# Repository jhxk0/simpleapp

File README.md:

# Drone stack: F405 flight controller + 4-in-1 AM32 ESC

Two KiCad 9 boards for a 5" quad, 30.5 x 30.5 mm M3 mounting.

| Board | Size | Layers | Key parts |
|---|---|---|---|
| `fc/`  flight controller | 36 x 36 mm | 4 (1 oz) | STM32F405RGT6, ICM-42688-P, BMP280, W25Q128 16 MB, LMR33630 5 V/3 A buck, USB-C |
| `esc/` 4-in-1 ESC (rev C) | 46 x 46 mm | 6 (2 oz outer, >=1 oz inner) | 4x STM32G071K8U6N (AM32), 12x LM2105, 24x CSD18543Q3A 60 V |

**Status:** the FC is complete: ERC clean, DRC clean with schematic parity, and fab files generated.
The ESC **schematic** is complete and ERC clean. Its **layout is about 95 % routed and DRC-clean apart from
29 open signal connections**, so it **must not be ordered yet**. See "ESC layout status" below.

Input: 3-6S LiPo. Both boards are generated from Python sources in `tools/`. Edit `tools/*_design.py`
(circuit) or `tools/*_layout.py` (placement), then rebuild; don't hand-edit the generated files unless
you're taking over in the KiCad GUI from here (which is fine — they are normal KiCad 9 projects).

## Files

```
fc/fc.kicad_pro, .kicad_sch, .kicad_pcb     KiCad 9 project (open in KiCad 9+)
fc/fc-schematic.pdf                         schematic
fc/fab/fc-gerbers.zip                       Gerbers + drill -> upload to the PCB fab
fc/fab/fc-BOM-jlcpcb.csv, fc-CPL-jlcpcb.csv JLCPCB assembly files
fc/fab/fc-BOM-full.csv                      BOM with MPNs and sourcing status
fc/drc.json, fc/erc.json                    last DRC / ERC reports
esc/esc.kicad_sch, esc-schematic.pdf        ESC schematic (complete)
esc/esc.kicad_pcb                           ESC layout, WIP: fully placed, power + gate drive done, 29 signal links open
tools/                                      generators (see "Rebuilding")
```

## FC <-> ESC link (8-pin JST-SH 1.0 mm, same pinout on both boards)

| Pin | 1 | 2 | 3 | 4 | 5 | 6 | 7 | 8 |
|---|---|---|---|---|---|---|---|---|
| Signal | VBAT | GND | CURR | TLM | M1 | M2 | M3 | M4 |

Use a straight-through cable (pin 1 to pin 1). This is *not* guaranteed to match third-party ESCs —
check before plugging the FC into anything else. This ESC has no current sensor: CURR (pin 3) is not
connected, so disable the current meter in firmware (or use a third-party ESC that provides it).
TLM is not driven either; use bidirectional DShot for RPM telemetry.
The SH contacts are rated ~1 A: power a high-draw VTX from the battery pads, not through the FC.

## Flight controller pinout (STM32F405RGT6) — for your firmware

| Function | Pins | Peripheral |
|---|---|---|
| IMU ICM-42688-P | PA5 SCK, PA6 MISO, PA7 MOSI, PA4 CS, PC4 INT1 | SPI1 |
| Flash W25Q128 (blackbox) | PC10 SCK, PC11 MISO, PC12 MOSI, PA15 CS | SPI3 |
| Baro BMP280 (addr 0x76) + GPS compass | PB8 SCL, PB9 SDA (2.2k pull-ups) | I2C1 |
| Motors M1-M4 (DShot) | PB0, PB1, PC8, PC9 | TIM3 CH3/CH4, TIM8 CH3/CH4 |
| Receiver (JST "RX") | PA9 TX, PA10 RX | USART1 |
| GPS (JST "GPS") | PA2 TX, PA3 RX | USART2 |
| VTX / MSP (JST "VTX") | PB10 TX, PB11 RX; PC7 = SBUS-in pin 6 | USART3, USART6 RX |
| Spare pads TX4/RX4, TX6 | PA0, PA1, PC6 | UART4, USART6 TX |
| ESC telemetry | PD2 | UART5 RX (RX only — PC12 is used by SPI3) |
| LED strip | PA8 (33 R series) | TIM1 CH1 |
| Buzzer (low-side FET, BZ+ = 5 V) | PB6 | TIM4 CH1 |
| Status LEDs (active high) | PB4 blue, PB5 green | |
| VBAT sense | PC2, divider 10k/1k (x11) | ADC |
| Current sense from ESC | PC1 (1k + 100 nF) | ADC |
| USB detect | PC5, divider 10k/20k from VBUS | |
| USB FS | PA11 D-, PA12 D+ | OTG_FS (no VBUS sensing on PA9) |
| HSE | 8 MHz crystal | |
| Boot | BOOT button -> BOOT0 (DFU over USB) ; SWD pads DIO/CLK/RST/3V3/GND on the bottom | |

Power: VBAT -> LMR33630 buck -> +5 V (also fed from USB through a Schottky) -> two AP2112K-3.3
LDOs (one for MCU/peripherals, one dedicated to the IMU).

## ESC firmware

Each channel is pin-for-pin compatible with AM32 target **JUPITER_80_G071**
(`HARDWARE_GROUP_G0_L`, current ADC PA4, voltage ADC PA5, `TARGET_VOLTAGE_DIVIDER 285`), checked
against `Inc/targets.h` and `Mcu/g071/Src/comparator.c` in the AM32 repository:

| Function | G071 pin |
|---|---|
| Phase A/B/C high | PA10 / PA9 / PA8 (TIM1 CH3/CH2/CH1) |
| Phase A/B/C low | PB15 / PB0 / PA7 (TIM1 CH3N/CH2N/CH1N) |
| Signal in (DShot) | PC6 (TIM3 CH1) |
| BEMF A / B / C | PA0 (COMP1 INM) / PA2 (COMP2 INM) / PB7 (COMP2 INM) |
| Virtual neutral | PA1 (COMP1 INP) and PA3 (COMP2 INP), formed from the three divided BEMF signals (3 x 10k) |
| Voltage sense | PA5, 27.4k/1k (x28.4) |

The driver (LM2105) has non-inverting high and low inputs, matching AM32's default (no `USE_INVERTED_LOW`).
Flash the AM32 bootloader to each MCU once through its SWD pads (DIO*n*, CLK*n*, 3V3_*n*, GND on the
bottom), then use the normal AM32 configurator through the FC passthrough. Set dead time and motor
parameters in the configurator; the target's `MILLIVOLT_PER_AMP` is irrelevant because per-ESC current
is not sensed (PA4 is tied low).

Gates are driven directly by the LM2105 (no gate resistors); NRST is left to the internal reset circuit.

Rating: CSD18543Q3A is 60 V / 8.1 mOhm. Treat the board as **~30 A burst / ~20 A continuous per motor
with airflow**. Fine for typical 5" builds; not for high-kV 6S racing setups.

## ESC layout status (rev C, routing unfinished)

Rev C reworks the layout so the power stage routes deterministically:

- 46 x 46 mm (was 44), same 30.5 mm M3 holes: the extra millimetre per side gives the corners, where two
  ESCs' drivers meet, room for their bypass caps and input escapes.
- 6-layer stack-up: F power stage | In1 GND plane | In2, In3 signals | In4 VBAT plane | B control.
- Battery pads in the centre feed the GND/VBAT planes through 35 vias each.
- **Every half-bridge uses one fixed, hand-designed copper pattern**, rotated to all 12 positions:
  low-side gate straight down the F channel between the VBAT/GND feed strips; high-side gate and the
  switch node through that channel's gap on In2/In3 to vias beside the driver; boot cap, VDD bypass,
  driver ground and the HI/LI input escapes all fixed. These 48 driver-to-FET links were what stalled
  rev B; they are now complete and DRC-clean.
- Back-EMF dividers sit on the bottom under the FETs and leave through the bottom channel; the virtual
  neutral is formed at each MCU from the divided signals (3 x 10k), so no neutral wiring runs along the edges.
- "No tracks" rule areas keep routing out of the phase pours and feed strips.

Not done: **29 open connections on the MCU side** (neutral, PWM, SIG, voltage sense, 3.3 V, a few supplies),
mostly around the four MCUs on the bottom. Freerouting gets to ~29 after the MCU support parts were anchored to their pins; the extra grid router
(`tools/finish_route.py`) pre-routes the long PWM/BEMF lines but does not close the rest. The inner
layers still have plenty of free space, so these are ordinary short links. Two ways to finish:

1. In KiCad: open `esc/esc.kicad_pcb`, press `B` to refill zones, run DRC and route the listed
   unconnected items by hand. In2/In3 are mostly empty.
2. Improve the automation (a negotiated-congestion router, or moving the MCUs off the battery pads'
   footprint so their pins can drop vias directly), then `python3 tools/pipeline.py esc route`.

The FC also works with any off-the-shelf 30.5 mm 4-in-1 ESC (check its 8-pin pinout against the table above).

## Before you order — verification checklist

These could not be checked from inside the design environment (no access to datasheet sites or the
JLCPCB/LCSC catalogue). Each is a short check:

1. **ICM-42688-P footprint and reserved pins.** The design uses KiCad's generic
   `LGA-14_3x2.5mm_P0.5mm` footprint and leaves RESV pins 2, 3, 7, 10, 11 unconnected. Compare pin 1
   location, pad sizes and the RESV recommendations against the TDK datasheet.
2. **LCSC part numbers.** `*-BOM-full.csv` marks every line as *recalled* (from memory, likely right),
   *unverified* or *MISSING*. JLCPCB's BOM upload shows the actual match; pick equivalents for the
   missing lines (mostly 50 V caps and ESC silicon).
3. **Assembly rotations.** JLCPCB's parts library sometimes uses a different zero-rotation than KiCad
   (QFN, SOT-23, connectors). Check the placement preview at order time and rotate as needed.
4. **(ESC) Gate-drive LDO margin.** L78L10 is rated 30 V input; 6S is 25.2 V. The 22 R + 1 uF filter helps,
   but a **low-ESR electrolytic (35 V, 470–1000 uF) across the battery pads is mandatory**.
5. **First power-up.** Use a current-limited supply (or smoke stopper), no props, one board at a time.

## Ordering (JLCPCB)

- FC: 4 layers, 1.6 mm, 1 oz, upload `fc/fab/fc-gerbers.zip`; assembly on **both sides** with the BOM and CPL.
- Minimums used: 0.1 mm track, 0.127 mm space, 0.3/0.5 mm vias — within JLCPCB's standard 4-layer capability.
- Stack-up: In1 = solid GND reference plane; In2 = signals + GND fill. Pick JLC's standard 4-layer stack-up.

## Rebuilding

Requires KiCad 9 (`kicad-cli` and the `pcbnew` Python module), Java 25 and Freerouting 2.4.1. The tools
find them automatically on Linux, macOS and Windows; otherwise set `KICAD_CLI`, `KICAD_PYTHON`,
`FREEROUTING_JAR` and `JAVA` (see `tools/kienv.py`).

```
python3 tools/pipeline.py fc sch          # schematic + ERC + netlist cross-check
python3 tools/pipeline.py fc route 80 3   # place, fanout, Freerouting, pours, DRC (retries until clean)
python3 tools/pipeline.py fc fab          # Gerbers, drill, BOM, CPL, renders
```

`pipeline.py esc ...` runs the same steps for the ESC (it also pre-routes the PWM/BEMF lines and runs
the finishing router).

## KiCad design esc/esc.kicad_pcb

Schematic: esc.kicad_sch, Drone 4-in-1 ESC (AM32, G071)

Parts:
C1, C2, C3, C4, C18, C29, C40, C51: 10uF 50V; C_1206_3216Metric; MPN 1206 10uF 50V X5R/X7R
C5, C7: 1uF 50V; C_0805_2012Metric; MPN 0805 1uF 50V X5R/X7R
C6, C8, C9, C12, C14, C16, C20, C23, C25, C27, C31, C34, C36, C38, C42, C45, C47, C49: 1uF 25V; C_0603_1608Metric; MPN 0603 1uF 25V X5R/X7R
C10, C21, C32, C43: 1uF; C_0402_1005Metric; MPN 0402 1uF X5R/X7R; LCSC C52923
C11, C22, C33, C44: 100nF; C_0402_1005Metric; MPN 0402 100nF X5R/X7R; LCSC C1525
C13, C15, C17, C24, C26, C28, C35, C37, C39, C46, C48, C50: 220nF; C_0402_1005Metric; MPN 0402 220nF X5R/X7R
C19, C30, C41, C52: 100nF 50V; C_0603_1608Metric; MPN 0603 100nF 50V X5R/X7R
H1, H2, H3, H4: M3; MountingHole_3.2mm_M3
J1: FC; JST_SH_SM08B-SRSS-TB_1x08-1MP_P1.00mm_Horizontal; MPN SM08B-SRSS-TB
Q1, Q2, Q3, Q4, Q5, Q6, Q7, Q8, Q9, Q10, Q11, Q12, Q13, Q14, Q15, Q16, Q17, Q18, Q19, Q20, Q21, Q22, Q23, Q24: CSD18543Q3A; VSON-8_3.3x3.3mm_P0.65mm_NexFET; MPN CSD18543Q3A
R1, R2: 22; R_0603_1608Metric; MPN 0603 22 1%; LCSC C25092
R3, R15, R27, R39: 100; R_0402_1005Metric; MPN 0402 100 1%; LCSC C25076
R4, R16, R28, R40: 27.4k; R_0402_1005Metric; MPN 0402 27.4k 1%
R5, R17, R29, R41: 1k; R_0402_1005Metric; MPN 0402 1k 1%; LCSC C11702
R6, R9, R12, R18, R21, R24, R30, R33, R36, R42, R45, R48: 18k; R_0402_1005Metric; MPN 0402 18k 1%
R7, R10, R13, R19, R22, R25, R31, R34, R37, R43, R46, R49: 2k; R_0402_1005Metric; MPN 0402 2k 1%
R8, R11, R14, R20, R23, R26, R32, R35, R38, R44, R47, R50: 10k; R_0402_1005Metric; MPN 0402 10k 1%; LCSC C25744
TP1: BAT+; SolderWirePad_1x01_SMD_5x10mm
TP2: BAT-; SolderWirePad_1x01_SMD_5x10mm
TP3: TLM; TestPoint_Pad_1.0x1.0mm
TP4: DIO1; TestPoint_Pad_1.0x1.0mm
TP5: CLK1; TestPoint_Pad_1.0x1.0mm
TP6: 3V3_1; TestPoint_Pad_1.0x1.0mm
TP7: M1A; TestPoint_Pad_2.5x2.5mm
TP8: M1B; TestPoint_Pad_2.5x2.5mm
TP9: M1C; TestPoint_Pad_2.5x2.5mm
TP10: DIO2; TestPoint_Pad_1.0x1.0mm
TP11: CLK2; TestPoint_Pad_1.0x1.0mm
TP12: 3V3_2; TestPoint_Pad_1.0x1.0mm
TP13: M2A; TestPoint_Pad_2.5x2.5mm
TP14: M2B; TestPoint_Pad_2.5x2.5mm
TP15: M2C; TestPoint_Pad_2.5x2.5mm
TP16: DIO3; TestPoint_Pad_1.0x1.0mm
TP17: CLK3; TestPoint_Pad_1.0x1.0mm
TP18: 3V3_3; TestPoint_Pad_1.0x1.0mm
TP19: M3A; TestPoint_Pad_2.5x2.5mm
TP20: M3B; TestPoint_Pad_2.5x2.5mm
TP21: M3C; TestPoint_Pad_2.5x2.5mm
TP22: DIO4; TestPoint_Pad_1.0x1.0mm
TP23: CLK4; TestPoint_Pad_1.0x1.0mm
TP24: 3V3_4; TestPoint_Pad_1.0x1.0mm
TP25: M4A; TestPoint_Pad_2.5x2.5mm
TP26: M4B; TestPoint_Pad_2.5x2.5mm
TP27: M4C; TestPoint_Pad_2.5x2.5mm
U1, U2: L78L10; SOT-89-3; MPN L78L10ACUTR
U3, U8, U13, U18: STM32G071K8U6N; QFN-32-1EP_5x5mm_P0.5mm_EP3.45x3.45mm; MPN STM32G071K8U6N
U4, U9, U14, U19: MCP1703-3.3; SOT-23; MPN MCP1703AT-3302E/CB
U5, U6, U7, U10, U11, U12, U15, U16, U17, U20, U21, U22: LM2105; WSON-8-1EP_2x2mm_P0.5mm_EP0.9x1.6mm; MPN LM2105DSGR

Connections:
/+3V3_1: C10.1, C11.1, TP6.1, U3.4 (VDD), U4.2 (VO)
/+3V3_2: C21.1, C22.1, TP12.1, U8.4 (VDD), U9.2 (VO)
/+3V3_3: C32.1, C33.1, TP18.1, U13.4 (VDD), U14.2 (VO)
/+3V3_4: C43.1, C44.1, TP24.1, U18.4 (VDD), U19.2 (VO)
/+10V_A: C6.1, C9.1, C12.1, C14.1, C16.1, C20.1, C23.1, C25.1, C27.1, U1.1 (OUT), U4.3 (VI), U5.1 (GVDD), U6.1 (GVDD), U7.1 (GVDD), U9.3 (VI), U10.1 (GVDD), U11.1 (GVDD), U12.1 (GVDD)
/+10V_B: C8.1, C31.1, C34.1, C36.1, C38.1, C42.1, C45.1, C47.1, C49.1, U2.1 (OUT), U14.3 (VI), U15.1 (GVDD), U16.1 (GVDD), U17.1 (GVDD), U19.3 (VI), U20.1 (GVDD), U21.1 (GVDD), U22.1 (GVDD)
/E1_BEMF_A: R6.2, R7.1, R8.1, U3.7 (PA0)
/E1_BEMF_B: R9.2, R10.1, R11.1, U3.9 (PA2)
/E1_BEMF_C: R12.2, R13.1, R14.1, U3.31 (PB7)
/E1_BST_A: C13.1, U5.8 (BST)
/E1_BST_B: C15.1, U6.8 (BST)
/E1_BST_C: C17.1, U7.8 (BST)
/E1_GH_A: Q1.4 (G), U5.7 (GH)
/E1_GH_B: Q3.4 (G), U6.7 (GH)
/E1_GH_C: Q5.4 (G), U7.7 (GH)
/E1_GL_A: Q2.4 (G), U5.5 (GL)
/E1_GL_B: Q4.4 (G), U6.5 (GL)
/E1_GL_C: Q6.4 (G), U7.5 (GL)
/E1_HA: U3.21 (PA10/UCPD1_DBCC2), U5.2 (INH)
/E1_HB: U3.19 (PA9/UCPD1_DBCC1), U6.2 (INH)
/E1_HC: U3.18 (PA8), U7.2 (INH)
/E1_LA: U3.17 (PB15), U5.3 (INL)
/E1_LB: U3.15 (PB0), U6.3 (INL)
/E1_LC: U3.14 (PA7), U7.3 (INL)
/E1_NEUTRAL: R8.2, R11.2, R14.2, U3.8 (PA1), U3.10 (PA3)
/E1_PH_A: C13.2, Q1.1 (S), Q1.2 (S), Q1.3 (S), Q2.5 (D), R6.1, TP7.1, U5.6 (SH)
/E1_PH_B: C15.2, Q3.1 (S), Q3.2 (S), Q3.3 (S), Q4.5 (D), R9.1, TP8.1, U6.6 (SH)
/E1_PH_C: C17.2, Q5.1 (S), Q5.2 (S), Q5.3 (S), Q6.5 (D), R12.1, TP9.1, U7.6 (SH)
/E1_SIG: R3.2, U3.20 (PC6)
/E1_SWCLK: TP5.1, U3.25 (PA14)
/E1_SWDIO: TP4.1, U3.24 (PA13)
/E1_VSENSE: R4.2, R5.1, U3.12 (PA5)
/E2_BEMF_A: R18.2, R19.1, R20.1, U8.7 (PA0)
/E2_BEMF_B: R21.2, R22.1, R23.1, U8.9 (PA2)
/E2_BEMF_C: R24.2, R25.1, R26.1, U8.31 (PB7)
/E2_BST_A: C24.1, U10.8 (BST)
/E2_BST_B: C26.1, U11.8 (BST)
/E2_BST_C: C28.1, U12.8 (BST)
/E2_GH_A: Q7.4 (G), U10.7 (GH)
/E2_GH_B: Q9.4 (G), U11.7 (GH)
/E2_GH_C: Q11.4 (G), U12.7 (GH)
/E2_GL_A: Q8.4 (G), U10.5 (GL)
/E2_GL_B: Q10.4 (G), U11.5 (GL)
/E2_GL_C: Q12.4 (G), U12.5 (GL)
/E2_HA: U8.21 (PA10/UCPD1_DBCC2), U10.2 (INH)
/E2_HB: U8.19 (PA9/UCPD1_DBCC1), U11.2 (INH)
/E2_HC: U8.18 (PA8), U12.2 (INH)
/E2_LA: U8.17 (PB15), U10.3 (INL)
/E2_LB: U8.15 (PB0), U11.3 (INL)
/E2_LC: U8.14 (PA7), U12.3 (INL)
/E2_NEUTRAL: R20.2, R23.2, R26.2, U8.8 (PA1), U8.10 (PA3)
/E2_PH_A: C24.2, Q7.1 (S), Q7.2 (S), Q7.3 (S), Q8.5 (D), R18.1, TP13.1, U10.6 (SH)
/E2_PH_B: C26.2, Q9.1 (S), Q9.2 (S), Q9.3 (S), Q10.5 (D), R21.1, TP14.1, U11.6 (SH)
/E2_PH_C: C28.2, Q11.1 (S), Q11.2 (S), Q11.3 (S), Q12.5 (D), R24.1, TP15.1, U12.6 (SH)
/E2_SIG: R15.2, U8.20 (PC6)
/E2_SWCLK: TP11.1, U8.25 (PA14)
/E2_SWDIO: TP10.1, U8.24 (PA13)
/E2_VSENSE: R16.2, R17.1, U8.12 (PA5)
/E3_BEMF_A: R30.2, R31.1, R32.1, U13.7 (PA0)
/E3_BEMF_B: R33.2, R34.1, R35.1, U13.9 (PA2)
/E3_BEMF_C: R36.2, R37.1, R38.1, U13.31 (PB7)
/E3_BST_A: C35.1, U15.8 (BST)
/E3_BST_B: C37.1, U16.8 (BST)
/E3_BST_C: C39.1, U17.8 (BST)
/E3_GH_A: Q13.4 (G), U15.7 (GH)
/E3_GH_B: Q15.4 (G), U16.7 (GH)
/E3_GH_C: Q17.4 (G), U17.7 (GH)
/E3_GL_A: Q14.4 (G), U15.5 (GL)
/E3_GL_B: Q16.4 (G), U16.5 (GL)
/E3_GL_C: Q18.4 (G), U17.5 (GL)
/E3_HA: U13.21 (PA10/UCPD1_DBCC2), U15.2 (INH)
/E3_HB: U13.19 (PA9/UCPD1_DBCC1), U16.2 (INH)
/E3_HC: U13.18 (PA8), U17.2 (INH)
/E3_LA: U13.17 (PB15), U15.3 (INL)
/E3_LB: U13.15 (PB0), U16.3 (INL)
/E3_LC: U13.14 (PA7), U17.3 (INL)
/E3_NEUTRAL: R32.2, R35.2, R38.2, U13.8 (PA1), U13.10 (PA3)
/E3_PH_A: C35.2, Q13.1 (S), Q13.2 (S), Q13.3 (S), Q14.5 (D), R30.1, TP19.1, U15.6 (SH)
/E3_PH_B: C37.2, Q15.1 (S), Q15.2 (S), Q15.3 (S), Q16.5 (D), R33.1, TP20.1, U16.6 (SH)
/E3_PH_C: C39.2, Q17.1 (S), Q17.2 (S), Q17.3 (S), Q18.5 (D), R36.1, TP21.1, U17.6 (SH)
/E3_SIG: R27.2, U13.20 (PC6)
/E3_SWCLK: TP17.1, U13.25 (PA14)
/E3_SWDIO: TP16.1, U13.24 (PA13)
/E3_VSENSE: R28.2, R29.1, U13.12 (PA5)
/E4_BEMF_A: R42.2, R43.1, R44.1, U18.7 (PA0)
/E4_BEMF_B: R45.2, R46.1, R47.1, U18.9 (PA2)
/E4_BEMF_C: R48.2, R49.1, R50.1, U18.31 (PB7)
/E4_BST_A: C46.1, U20.8 (BST)
/E4_BST_B: C48.1, U21.8 (BST)
/E4_BST_C: C50.1, U22.8 (BST)
/E4_GH_A: Q19.4 (G), U20.7 (GH)
/E4_GH_B: Q21.4 (G), U21.7 (GH)
/E4_GH_C: Q23.4 (G), U22.7 (GH)
/E4_GL_A: Q20.4 (G), U20.5 (GL)
/E4_GL_B: Q22.4 (G), U21.5 (GL)
/E4_GL_C: Q24.4 (G), U22.5 (GL)
/E4_HA: U18.21 (PA10/UCPD1_DBCC2), U20.2 (INH)
/E4_HB: U18.19 (PA9/UCPD1_DBCC1), U21.2 (INH)
/E4_HC: U18.18 (PA8), U22.2 (INH)
/E4_LA: U18.17 (PB15), U20.3 (INL)
/E4_LB: U18.15 (PB0), U21.3 (INL)
/E4_LC: U18.14 (PA7), U22.3 (INL)
/E4_NEUTRAL: R44.2, R47.2, R50.2, U18.8 (PA1), U18.10 (PA3)
/E4_PH_A: C46.2, Q19.1 (S), Q19.2 (S), Q19.3 (S), Q20.5 (D), R42.1, TP25.1, U20.6 (SH)
/E4_PH_B: C48.2, Q21.1 (S), Q21.2 (S), Q21.3 (S), Q22.5 (D), R45.1, TP26.1, U21.6 (SH)
/E4_PH_C: C50.2, Q23.1 (S), Q23.2 (S), Q23.3 (S), Q24.5 (D), R48.1, TP27.1, U22.6 (SH)
/E4_SIG: R39.2, U18.20 (PC6)
/E4_SWCLK: TP23.1, U18.25 (PA14)
/E4_SWDIO: TP22.1, U18.24 (PA13)
/E4_VSENSE: R40.2, R41.1, U18.12 (PA5)
/GND: C1.2, C2.2, C3.2, C4.2, C5.2, C6.2, C7.2, C8.2, C9.2, C10.2, C11.2, C12.2, C14.2, C16.2, C18.2, C19.2, C20.2, C21.2, C22.2, C23.2, C25.2, C27.2, C29.2, C30.2, C31.2, C32.2, C33.2, C34.2, C36.2, C38.2, C40.2, C41.2, C42.2, C43.2, C44.2, C45.2, C47.2, C49.2, C51.2, C52.2, J1.2, Q2.1 (S), Q2.2 (S), Q2.3 (S), Q4.1 (S), Q4.2 (S), Q4.3 (S), Q6.1 (S), Q6.2 (S), Q6.3 (S), Q8.1 (S), Q8.2 (S), Q8.3 (S), Q10.1 (S), Q10.2 (S), Q10.3 (S), Q12.1 (S), Q12.2 (S), Q12.3 (S), Q14.1 (S), Q14.2 (S), Q14.3 (S), Q16.1 (S), Q16.2 (S), Q16.3 (S), Q18.1 (S), Q18.2 (S), Q18.3 (S), Q20.1 (S), Q20.2 (S), Q20.3 (S), Q22.1 (S), Q22.2 (S), Q22.3 (S), Q24.1 (S), Q24.2 (S), Q24.3 (S), R5.2, R7.2, R10.2, R13.2, R17.2, R19.2, R22.2, R25.2, R29.2, R31.2, R34.2, R37.2, R41.2, R43.2, R46.2, R49.2, TP2.1, U1.2 (GND), U2.2 (GND), U3.5 (VSS), U3.11 (PA4), U3.33 (VSS), U4.1 (GND), U5.4 (GND), U5.9 (GND), U6.4 (GND), U6.9 (GND), U7.4 (GND), U7.9 (GND), U8.5 (VSS), U8.11 (PA4), U8.33 (VSS), U9.1 (GND), U10.4 (GND), U10.9 (GND), U11.4 (GND), U11.9 (GND), U12.4 (GND), U12.9 (GND), U13.5 (VSS), U13.11 (PA4), U13.33 (VSS), U14.1 (GND), U15.4 (GND), U15.9 (GND), U16.4 (GND), U16.9 (GND), U17.4 (GND), U17.9 (GND), U18.5 (VSS), U18.11 (PA4), U18.33 (VSS), U19.1 (GND), U20.4 (GND), U20.9 (GND), U21.4 (GND), U21.9 (GND), U22.4 (GND), U22.9 (GND)
/SIG1: J1.5, R3.1
/SIG2: J1.6, R15.1
/SIG3: J1.7, R27.1
/SIG4: J1.8, R39.1
/TLM: J1.4, TP3.1
/VBAT: C1.1, C2.1, C3.1, C4.1, C18.1, C19.1, C29.1, C30.1, C40.1, C41.1, C51.1, C52.1, J1.1, Q1.5 (D), Q3.5 (D), Q5.5 (D), Q7.5 (D), Q9.5 (D), Q11.5 (D), Q13.5 (D), Q15.5 (D), Q17.5 (D), Q19.5 (D), Q21.5 (D), Q23.5 (D), R1.1, R2.1, R4.1, R16.1, R28.1, R40.1, TP1.1
/VFILT_A: C5.1, R1.2, U1.3 (IN)
/VFILT_B: C7.1, R2.2, U2.3 (IN)

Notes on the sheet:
BATTERY & SENSE
GATE DRIVE SUPPLY
FC CONNECTOR
ESC1 MCU
ESC1 POWER STAGE
ESC2 MCU
ESC2 POWER STAGE
ESC3 MCU
ESC3 POWER STAGE
ESC4 MCU
ESC4 POWER STAGE
MECHANICAL

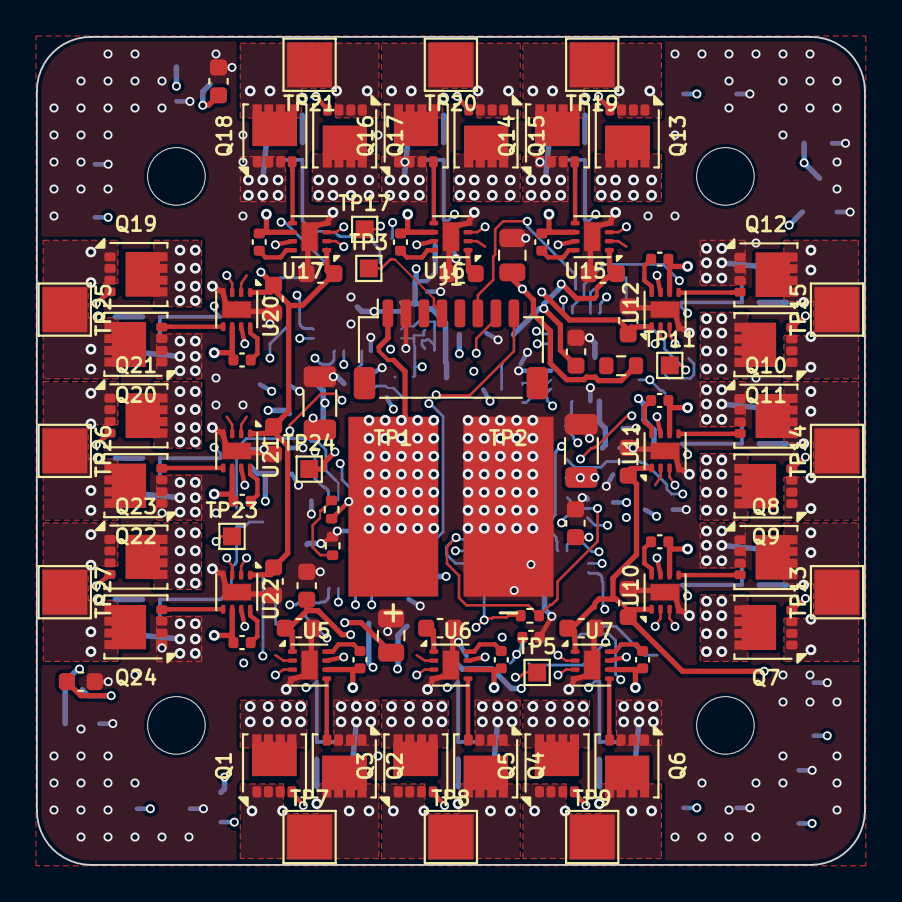
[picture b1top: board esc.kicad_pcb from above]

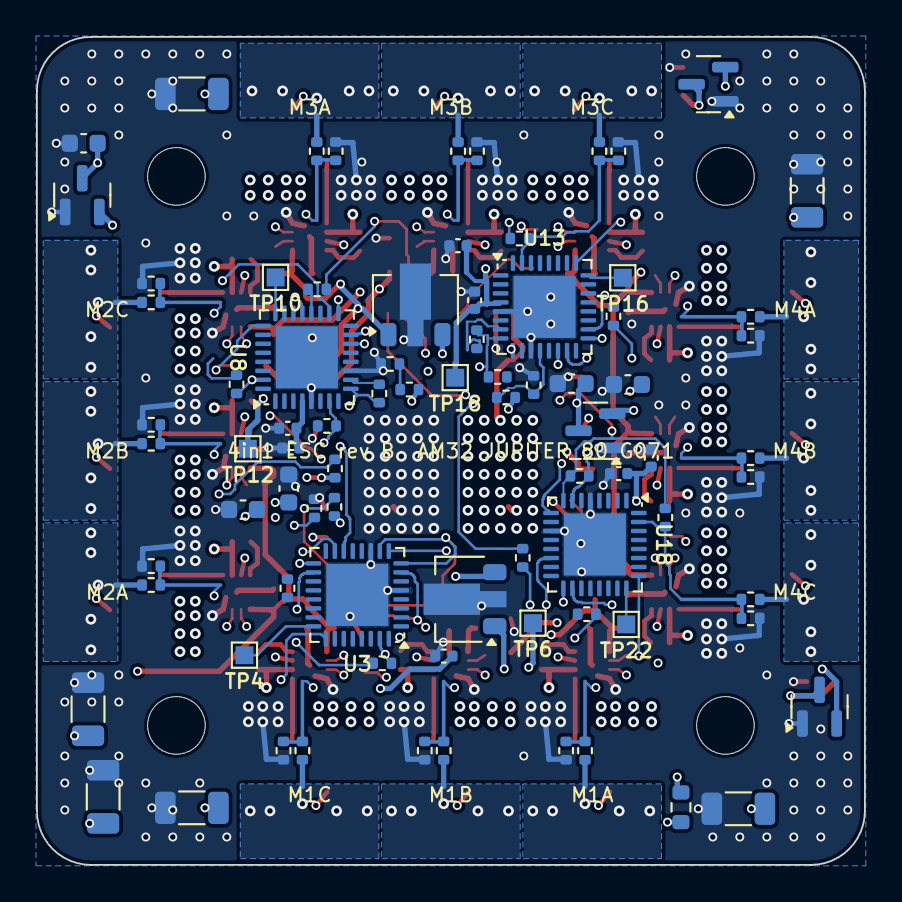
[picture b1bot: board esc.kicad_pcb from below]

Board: 6 copper layers, 46.0 x 46.0 mm, 180 parts (81 on the bottom side), 119 nets.

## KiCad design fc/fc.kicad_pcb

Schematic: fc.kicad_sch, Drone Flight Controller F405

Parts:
C1, C2, C3, C4, C7, C10, C16, C24, C25, C26, C27, C29, C30: 100nF; C_0402_1005Metric; MPN 0402 100nF X5R/X7R; LCSC C1525
C5: 4.7uF; C_0603_1608Metric; MPN 0603 4.7uF X5R/X7R; LCSC C19666
C6, C17, C20, C21, C22, C23: 1uF; C_0402_1005Metric; MPN 0402 1uF X5R/X7R; LCSC C52923
C8, C9, C28: 2.2uF; C_0402_1005Metric; MPN 0402 2.2uF X5R/X7R; LCSC C12530
C11, C12: 33pF; C_0402_1005Metric; MPN 0402 33pF X5R/X7R; LCSC C1562
C13, C14: 10uF 50V; C_1206_3216Metric; MPN 1206 10uF 50V X5R/X7R
C15: 100nF 50V; C_0603_1608Metric; MPN 0603 100nF 50V X5R/X7R
C18, C19: 22uF 10V; C_0805_2012Metric; MPN 0805 22uF 10V X5R/X7R; LCSC C45783
D1: RED; LED_0603_1608Metric; MPN 0603 red; LCSC C2286
D2, D5: B5819W; D_SOD-123; MPN B5819W; LCSC C8598
D3: BLUE; LED_0603_1608Metric; MPN 0603 blue; LCSC C72041
D4: GREEN; LED_0603_1608Metric; MPN 0603 green; LCSC C72043
FB1: 600R@100MHz; L_0402_1005Metric; MPN BLM15AG601SN1D
H1, H2, H3, H4: M3; MountingHole_3.2mm_M3
J1: USB-C; USB_C_Receptacle_HRO_TYPE-C-31-M-12; MPN TYPE-C-31-M-12; LCSC C165948
J2: ESC; JST_SH_SM08B-SRSS-TB_1x08-1MP_P1.00mm_Horizontal; MPN SM08B-SRSS-TB
J3: RX; JST_SH_SM04B-SRSS-TB_1x04-1MP_P1.00mm_Horizontal; MPN SM04B-SRSS-TB
J4: GPS; JST_SH_SM06B-SRSS-TB_1x06-1MP_P1.00mm_Horizontal; MPN SM06B-SRSS-TB
J5: VTX; JST_SH_SM06B-SRSS-TB_1x06-1MP_P1.00mm_Horizontal; MPN SM06B-SRSS-TB
L1: 4.7uH; L_Bourns-SRN4018; MPN SRN4018-4R7M (Isat 2.5A)
Q1: AO3400A; SOT-23; MPN AO3400A; LCSC C20917
R1, R2, R8, R11, R17, R18, R19, R23: 10k; R_0402_1005Metric; MPN 0402 10k 1%; LCSC C25744
R3, R5: 100k; R_0402_1005Metric; MPN 0402 100k 1%; LCSC C25741
R4: 27k; R_0402_1005Metric; MPN 0402 27k 1%; LCSC C25771
R6: 24.9k; R_0402_1005Metric; MPN 0402 24.9k 1%
R7: 1.5k; R_0402_1005Metric; MPN 0402 1.5k 1%; LCSC C25867
R9, R10, R20, R21: 1k; R_0402_1005Metric; MPN 0402 1k 1%; LCSC C11702
R12: 20k; R_0402_1005Metric; MPN 0402 20k 1%; LCSC C25765
R13, R14: 5.1k; R_0402_1005Metric; MPN 0402 5.1k 1%; LCSC C25905
R15, R16: 2.2k; R_0402_1005Metric; MPN 0402 2.2k 1%; LCSC C25879
R22: 100; R_0402_1005Metric; MPN 0402 100 1%; LCSC C25076
R24: 33; R_0402_1005Metric; MPN 0402 33 1%; LCSC C25105
SW1: BOOT; SW_Push_1P1T_NO_CK_KMR2; MPN KMR211NGLFS
TP1: UART4_TX; TestPoint_Pad_1.5x1.5mm
TP2: UART4_RX; TestPoint_Pad_1.5x1.5mm
TP3: UART6_TX; TestPoint_Pad_1.5x1.5mm
TP4: LED_STRIP; TestPoint_Pad_1.5x1.5mm
TP5, TP8: +5V; TestPoint_Pad_1.5x1.5mm
TP6: GND; TestPoint_Pad_1.5x1.5mm
TP7: BUZ-; TestPoint_Pad_1.5x1.5mm
TP9: SWDIO; TestPoint_Pad_1.0x1.0mm
TP10: SWCLK; TestPoint_Pad_1.0x1.0mm
TP11: NRST; TestPoint_Pad_1.0x1.0mm
TP12: +3V3; TestPoint_Pad_1.0x1.0mm
TP13: GND; TestPoint_Pad_1.0x1.0mm
U1: STM32F405RGT6; LQFP-64_10x10mm_P0.5mm; MPN STM32F405RGT6; LCSC C15742
U2: LMR33630BDDA; Texas_HSOP-8-1EP_3.9x4.9mm_P1.27mm_ThermalVias; MPN LMR33630BDDAR
U3, U4: AP2112K-3.3; SOT-23-5; MPN AP2112K-3.3TRG1; LCSC C51118
U5: USBLC6-2SC6; SOT-23-6; MPN USBLC6-2SC6; LCSC C7519
U6: ICM-42688-P; LGA-14_3x2.5mm_P0.5mm_LayoutBorder3x4y; MPN ICM-42688-P; LCSC C1850418
U7: BMP280; Bosch_LGA-8_2x2.5mm_P0.65mm_ClockwisePinNumbering; MPN BMP280; LCSC C83291
U8: W25Q128JVSIQ; SOIC-8_5.3x5.3mm_P1.27mm; MPN W25Q128JVSIQ; LCSC C97521
Y1: 8MHz; Crystal_SMD_3225-4Pin_3.2x2.5mm; MPN X322508MSB4SI (8MHz, 20pF CL); LCSC C9002

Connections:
/+3V3: C1.1, C2.1, C3.1, C4.1, C5.1, C21.1, C29.1, C30.1, D1.2 (A), FB1.1, R15.1, R16.1, R17.1, R18.1, R19.1, SW1.1, TP12.1, U1.1 (VBAT), U1.19 (VDD), U1.32 (VDD), U1.48 (VDD), U1.64 (VDD), U3.5 (VOUT), U7.2 (CSB), U7.6 (VDDIO), U7.8 (VDD), U8.8 (VCC)
/+3V3_IMU: C23.1, C26.1, C27.1, C28.1, U4.5 (VOUT), U6.5 (VDDIO), U6.8 (VDD)
/+5V: C18.1, C19.1, C20.1, C22.1, D2.1 (K), D5.1 (K), J3.1, J4.1, L1.2, R5.1, TP5.1, TP8.1, U3.1 (VIN), U3.3 (EN), U4.1 (VIN), U4.3 (EN)
/BOOT0: R1.1, SW1.2, U1.60 (BOOT0)
/BOOT1: R2.1, U1.28 (PB2)
/BUCK_BOOT: C16.1, U2.7 (BOOT)
/BUCK_EN: R3.2, R4.1, U2.3 (EN)
/BUCK_FB: R5.2, R6.1, U2.5 (FB)
/BUCK_SW: C16.2, L1.1, U2.8 (SW)
/BUCK_VCC: C17.1, U2.6 (VCC)
/BUZ-: D5.2 (A), Q1.3 (D), TP7.1
/BUZZER_MCU: R22.1, U1.58 (PB6)
/BUZ_G: Q1.1 (G), R22.2, R23.1
/CC1: J1.A5 (CC1), R13.1
/CC2: J1.B5 (CC2), R14.1
/CURR: J2.3, R10.1
/CURR_ADC: C25.1, R10.2, U1.9 (PC1)
/ESC_TLM: J2.4, U1.54 (PD2)
/FLASH_CS: R17.2, U1.50 (PA15), U8.1 (~CS)
/FLASH_HOLD: R19.2, U8.7 (~HOLD/~RESET/IO_{3})
/FLASH_MISO: U1.52 (PC11), U8.2 (DO/IO_{1})
/FLASH_MOSI: U1.53 (PC12), U8.5 (DI/IO_{0})
/FLASH_SCK: U1.51 (PC10), U8.6 (CLK)
/FLASH_WP: R18.2, U8.3 (~WP/IO_{2})
/GND: C1.2, C2.2, C3.2, C4.2, C5.2, C6.2, C7.2, C8.2, C9.2, C10.2, C11.2, C12.2, C13.2, C14.2, C15.2, C17.2, C18.2, C19.2, C20.2, C21.2, C22.2, C23.2, C24.2, C25.2, C26.2, C27.2, C28.2, C29.2, C30.2, J1.A1 (GND), J1.A12 (GND), J1.B1 (GND), J1.B12 (GND), J1.S1 (SHIELD), J2.2, J3.2, J4.2, J5.2, J5.5, Q1.2 (S), R1.2, R2.2, R4.2, R6.2, R7.2, R9.2, R12.2, R13.2, R14.2, R20.2, R21.2, R23.2, TP6.1, TP13.1, U1.12 (VSSA), U1.18 (VSS), U1.63 (VSS), U2.1 (GND), U2.9 (GND), U3.2 (GND), U4.2 (GND), U5.2 (GND), U6.6 (GND), U7.1 (GND), U7.5 (SDO), U7.7 (GND), U8.4 (GND), Y1.2, Y1.4
/HSE_IN: C11.1, U1.5 (PH0), Y1.1
/HSE_OUT: C12.1, U1.6 (PH1), Y1.3
/I2C_SCL: J4.5, R15.2, U1.61 (PB8), U7.4 (SCK)
/I2C_SDA: J4.6, R16.2, U1.62 (PB9), U7.3 (SDI)
/IMU_CS: U1.20 (PA4), U6.12 (AP_CS)
/IMU_INT1: U1.24 (PC4), U6.4 (INT1)
/IMU_MISO: U1.22 (PA6), U6.1 (AP_SDO)
/IMU_MOSI: U1.23 (PA7), U6.14 (AP_SDI)
/IMU_SCK: U1.21 (PA5), U6.13 (AP_SCLK)
/LED1_K: D3.1 (K), R20.1
/LED2_K: D4.1 (K), R21.1
/LED_PWR_K: D1.1 (K), R7.1
/LED_STAT1: D3.2 (A), U1.56 (PB4)
/LED_STAT2: D4.2 (A), U1.57 (PB5)
/LED_STRIP: R24.2, TP4.1
/LED_STRIP_MCU: R24.1, U1.41 (PA8)
/M1: J2.5, U1.26 (PB0)
/M2: J2.6, U1.27 (PB1)
/M3: J2.7, U1.39 (PC8)
/M4: J2.8, U1.40 (PC9)
/NRST: C10.1, TP11.1, U1.7 (NRST)
/SWCLK: TP10.1, U1.49 (PA14)
/SWDIO: TP9.1, U1.46 (PA13)
/UART1_RX: J3.4, U1.43 (PA10)
/UART1_TX: J3.3, U1.42 (PA9)
/UART2_RX: J4.4, U1.17 (PA3)
/UART2_TX: J4.3, U1.16 (PA2)
/UART3_RX: J5.4, U1.30 (PB11)
/UART3_TX: J5.3, U1.29 (PB10)
/UART4_RX: TP2.1, U1.15 (PA1)
/UART4_TX: TP1.1, U1.14 (PA0)
/UART6_RX: J5.6, U1.38 (PC7)
/UART6_TX: TP3.1, U1.37 (PC6)
/USB_CONN_DM: J1.A7 (D-), J1.B7 (D-), U5.1 (I/O1)
/USB_CONN_DP: J1.A6 (D+), J1.B6 (D+), U5.3 (I/O2)
/USB_DET: R11.2, R12.1, U1.25 (PC5)
/USB_DM: U1.44 (PA11), U5.6 (I/O1)
/USB_DP: U1.45 (PA12), U5.4 (I/O2)
/VBAT: C13.1, C14.1, C15.1, J2.1, J5.1, R3.1, R8.1, U2.2 (VIN)
/VBAT_ADC: C24.1, R8.2, R9.1, U1.10 (PC2)
/VBUS: D2.2 (A), J1.A4 (VBUS), J1.A9 (VBUS), J1.B4 (VBUS), J1.B9 (VBUS), R11.1, U5.5 (VBUS)
/VCAP1: C8.1, U1.31 (VCAP_1)
/VCAP2: C9.1, U1.47 (VCAP_2)
/VDDA: C6.1, C7.1, FB1.2, U1.13 (VDDA)

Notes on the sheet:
MCU
CLOCK
POWER 5V
POWER 3V3
SENSING
USB
IMU
BARO
FLASH
CONNECTORS
PADS
MECHANICAL

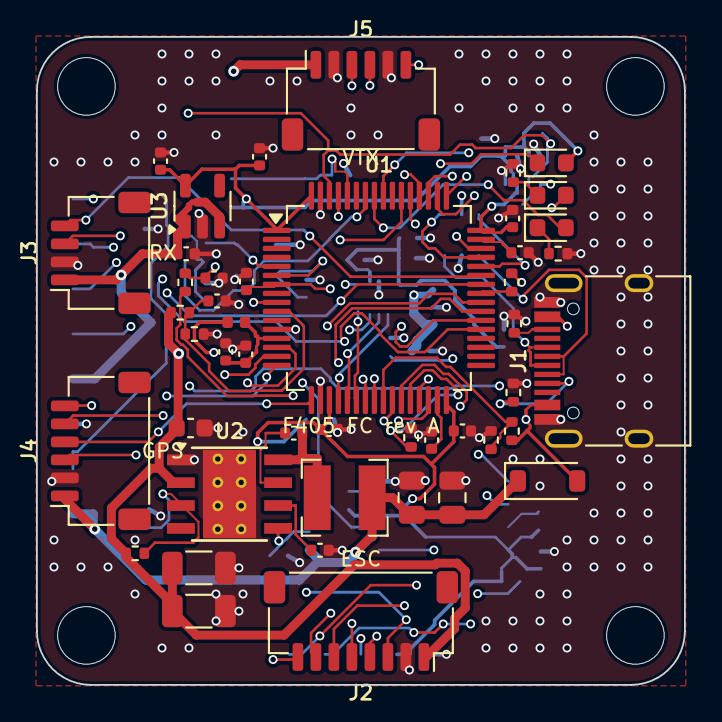
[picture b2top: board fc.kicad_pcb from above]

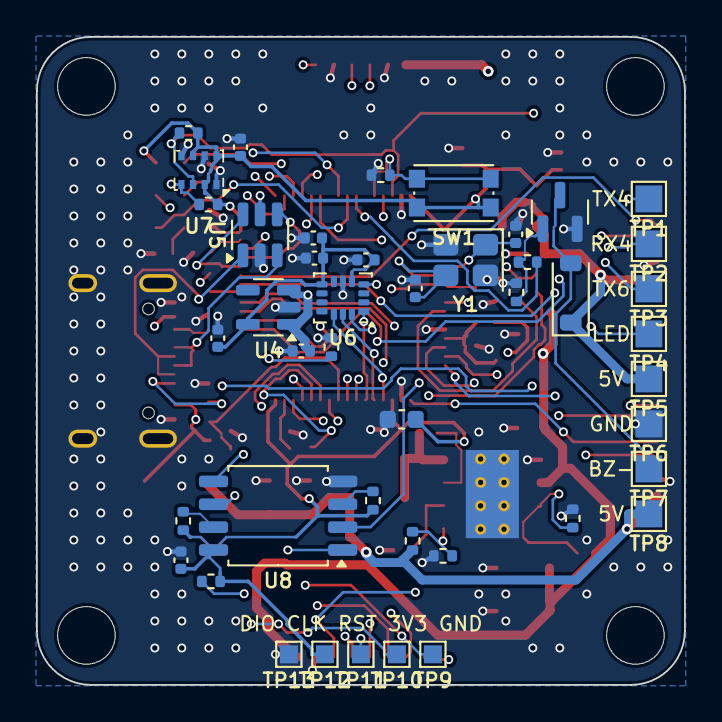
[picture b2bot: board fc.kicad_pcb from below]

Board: 4 copper layers, 36.0 x 36.0 mm, 94 parts (44 on the bottom side), 69 nets.

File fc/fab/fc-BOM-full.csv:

Qty,Designators,Value,MPN / spec,Footprint,LCSC,LCSC status,Notes
1,U1,STM32F405RGT6,STM32F405RGT6,LQFP-64_10x10mm_P0.5mm,C15742,recalled - confirm in JLC BOM tool,
13,C1 C2 C3 C4 C7 C10 C16 C24 C25 C26 C27 C29 C30,100nF,0402 100nF  X5R/X7R,C_0402_1005Metric,C1525,recalled - confirm in JLC BOM tool,
1,C5,4.7uF,0603 4.7uF  X5R/X7R,C_0603_1608Metric,C19666,recalled - confirm in JLC BOM tool,
1,FB1,600R@100MHz,BLM15AG601SN1D,L_0402_1005Metric,,MISSING - pick an equivalent,
6,C6 C17 C20 C21 C22 C23,1uF,0402 1uF  X5R/X7R,C_0402_1005Metric,C52923,recalled - confirm in JLC BOM tool,
3,C8 C9 C28,2.2uF,0402 2.2uF  X5R/X7R,C_0402_1005Metric,C12530,recalled - confirm in JLC BOM tool,
8,R1 R2 R8 R11 R17 R18 R19 R23,10k,0402 10k 1%,R_0402_1005Metric,C25744,recalled - confirm in JLC BOM tool,
1,SW1,BOOT,KMR211NGLFS,SW_Push_1P1T_NO_CK_KMR2,,MISSING - pick an equivalent,
1,Y1,8MHz,"X322508MSB4SI (8MHz, 20pF CL)",Crystal_SMD_3225-4Pin_3.2x2.5mm,C9002,unverified,load caps sized for CL=20pF
2,C11 C12,33pF,0402 33pF  X5R/X7R,C_0402_1005Metric,C1562,recalled - confirm in JLC BOM tool,
1,U2,LMR33630BDDA,LMR33630BDDAR,Texas_HSOP-8-1EP_3.9x4.9mm_P1.27mm_ThermalVias,,MISSING - pick an equivalent,PG unused
2,C13 C14,10uF 50V,1206 10uF 50V X5R/X7R,C_1206_3216Metric,,MISSING - pick an equivalent,
1,C15,100nF 50V,0603 100nF 50V X5R/X7R,C_0603_1608Metric,,MISSING - pick an equivalent,
2,R3 R5,100k,0402 100k 1%,R_0402_1005Metric,C25741,recalled - confirm in JLC BOM tool,
1,R4,27k,0402 27k 1%,R_0402_1005Metric,C25771,recalled - confirm in JLC BOM tool,
1,L1,4.7uH,SRN4018-4R7M (Isat 2.5A),L_Bourns-SRN4018,,MISSING - pick an equivalent,
1,R6,24.9k,0402 24.9k 1%,R_0402_1005Metric,,MISSING - pick an equivalent,
2,C18 C19,22uF 10V,0805 22uF 10V X5R/X7R,C_0805_2012Metric,C45783,recalled - confirm in JLC BOM tool,
2,U3 U4,AP2112K-3.3,AP2112K-3.3TRG1,SOT-23-5,C51118,recalled - confirm in JLC BOM tool,dedicated IMU supply
1,D1,RED,0603 red,LED_0603_1608Metric,C2286,recalled - confirm in JLC BOM tool,
1,R7,1.5k,0402 1.5k 1%,R_0402_1005Metric,C25867,recalled - confirm in JLC BOM tool,
4,R9 R10 R20 R21,1k,0402 1k 1%,R_0402_1005Metric,C11702,recalled - confirm in JLC BOM tool,
1,R12,20k,0402 20k 1%,R_0402_1005Metric,C25765,recalled - confirm in JLC BOM tool,
1,J1,USB-C,TYPE-C-31-M-12,USB_C_Receptacle_HRO_TYPE-C-31-M-12,C165948,recalled - confirm in JLC BOM tool,
2,R13 R14,5.1k,0402 5.1k 1%,R_0402_1005Metric,C25905,recalled - confirm in JLC BOM tool,
1,U5,USBLC6-2SC6,USBLC6-2SC6,SOT-23-6,C7519,recalled - confirm in JLC BOM tool,
2,D2 D5,B5819W,B5819W,D_SOD-123,C8598,recalled - confirm in JLC BOM tool,USB powers 5V rail; blocks backfeed; buzzer flyback
1,U6,ICM-42688-P,ICM-42688-P,LGA-14_3x2.5mm_P0.5mm_LayoutBorder3x4y,C1850418,recalled - confirm in JLC BOM tool,verify footprint pin-1 vs datasheet
1,U7,BMP280,BMP280,Bosch_LGA-8_2x2.5mm_P0.65mm_ClockwisePinNumbering,C83291,recalled - confirm in JLC BOM tool,I2C addr 0x76
2,R15 R16,2.2k,0402 2.2k 1%,R_0402_1005Metric,C25879,recalled - confirm in JLC BOM tool,
1,U8,W25Q128JVSIQ,W25Q128JVSIQ,SOIC-8_5.3x5.3mm_P1.27mm,C97521,recalled - confirm in JLC BOM tool,
1,D3,BLUE,0603 blue,LED_0603_1608Metric,C72041,recalled - confirm in JLC BOM tool,
1,D4,GREEN,0603 green,LED_0603_1608Metric,C72043,recalled - confirm in JLC BOM tool,
1,Q1,AO3400A,AO3400A,SOT-23,C20917,recalled - confirm in JLC BOM tool,
1,R22,100,0402 100 1%,R_0402_1005Metric,C25076,recalled - confirm in JLC BOM tool,
1,R24,33,0402 33 1%,R_0402_1005Metric,C25105,recalled - confirm in JLC BOM tool,
1,J2,ESC,SM08B-SRSS-TB,JST_SH_SM08B-SRSS-TB_1x08-1MP_P1.00mm_Horizontal,,MISSING - pick an equivalent,
1,J3,RX,SM04B-SRSS-TB,JST_SH_SM04B-SRSS-TB_1x04-1MP_P1.00mm_Horizontal,,MISSING - pick an equivalent,
1,J4,GPS,SM06B-SRSS-TB,JST_SH_SM06B-SRSS-TB_1x06-1MP_P1.00mm_Horizontal,,MISSING - pick an equivalent,
1,J5,VTX,SM06B-SRSS-TB,JST_SH_SM06B-SRSS-TB_1x06-1MP_P1.00mm_Horizontal,,MISSING - pick an equivalent,

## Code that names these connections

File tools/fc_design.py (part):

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mcu = {
    "VBAT": "+3V3", "VDD": "+3V3", "VSS": GND, "VDDA": "VDDA", "VSSA": GND,
    "VCAP_1": "VCAP1", "VCAP_2": "VCAP2", "NRST": "NRST", "BOOT0": "BOOT0",
    "PH0": "HSE_IN", "PH1": "HSE_OUT",
    # USB
    "PA11": "USB_DM", "PA12": "USB_DP", "PC5": "USB_DET",
    # SWD
    "PA13": "SWDIO", "PA14": "SWCLK",
    # IMU on SPI1
    "PA4": "IMU_CS", "PA5": "IMU_SCK", "PA6": "IMU_MISO", "PA7": "IMU_MOSI", "PC4": "IMU_INT1",
    # Flash on SPI3
    "PA15": "FLASH_CS", "PC10": "FLASH_SCK", "PC11": "FLASH_MISO", "PC12": "FLASH_MOSI",
    # I2C1: baro + external compass
    "PB8": "I2C_SCL", "PB9": "I2C_SDA",
    # UARTs
    "PA9": "UART1_TX", "PA10": "UART1_RX",     # receiver
    "PA2": "UART2_TX", "PA3": "UART2_RX",      # GPS
    "PB10": "UART3_TX", "PB11": "UART3_RX",    # VTX / MSP
    "PA0": "UART4_TX", "PA1": "UART4_RX",      # spare pads
    "PC6": "UART6_TX", "PC7": "UART6_RX",      # VTX SBUS / spare
    "PD2": "ESC_TLM",                          # UART5_RX
    # Motors (DShot): TIM3 CH3/CH4, TIM8 CH3/CH4
    "PB0": "M1", "PB1": "M2", "PC8": "M3", "PC9": "M4",
    # Misc
    "PA8": "LED_STRIP_MCU",    # TIM1_CH1
    "PB6": "BUZZER_MCU",       # TIM4_CH1
    "PB4": "LED_STAT1", "PB5": "LED_STAT2",
    "PC1": "CURR_ADC", "PC2": "VBAT_ADC",
    "PB2": "BOOT1",
}
d.add("U", "MCU_ST_STM32F4:STM32F405RGTx", "STM32F405RGT6", "Package_QFP:LQFP-64_10x10mm_P0.5mm",
      mcu, mpn="STM32F405RGT6", lcsc="C15742", lcsc_ok=True)
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
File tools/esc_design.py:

"""4-in-1 ESC, 3-6S, 30.5mm mount.

Per channel: STM32G071K8U6N running AM32, pin-compatible with AM32 target JUPITER_80_G071
(HARDWARE_GROUP_G0_L, current ADC PA4, voltage ADC PA5, TARGET_VOLTAGE_DIVIDER 285), 3x LM2105
half-bridge drivers, 6x CSD18543Q3A (60V 8.1mOhm). Board-level: 2x 10V gate-drive LDOs. No total-current
sensor: FC connector pin 3 (CURR) is not connected.
"""
from design import Design

d = Design("esc", "Drone 4-in-1 ESC (AM32, G071)")
GND = "GND"
FET = "Transistor_FET:CSD18543Q3A"
FET_FP = "Package_SON:VSON-8_3.3x3.3mm_P0.65mm_NexFET"

# ---------------------------------------------------------------- shared power
d.group("Battery & sense")
PADBIG = "Connector_Wire:SolderWirePad_1x01_SMD_5x10mm"
# battery pads feed the VBAT / GND planes directly through via arrays (no shunt in the power path)
d.add("TP", "Connector:TestPoint", "BAT+", PADBIG, {"1": "VBAT"},
      note="also solder the low-ESR bulk electrolytic (35V, 470-1000uF) across BAT+/BAT- - mandatory")
d.add("TP", "Connector:TestPoint", "BAT-", PADBIG, {"1": GND})
for _ in range(4):
    d.C("10uF", "VBAT", GND, size="1206", volt="50V", lcsc="", lcsc_ok=False)
d.flag("VBAT"); d.flag(GND)

d.group("Gate drive supply")
for rail in ("A", "B"):        # A feeds ESC1+2, B feeds ESC3+4
    d.R("22", "VBAT", "VFILT_" + rail, size="0603")
    d.C("1uF", "VFILT_" + rail, GND, size="0805", volt="50V", lcsc="", lcsc_ok=False)
    d.flag("VFILT_" + rail)
    d.add("U", "Regulator_Linear:L78L10_SOT89", "L78L10", "Package_TO_SOT_SMD:SOT-89-3",
          {"3": "VFILT_" + rail, "2": GND, "1": "+10V_" + rail}, mpn="L78L10ACUTR")
    d.C("1uF", "+10V_" + rail, GND, size="0603", volt="25V", lcsc="", lcsc_ok=False)

d.group("FC connector")
d.add("J", "Connector_Generic:Conn_01x08", "FC",
      "Connector_JST:JST_SH_SM08B-SRSS-TB_1x08-1MP_P1.00mm_Horizontal",
      {"1": "VBAT", "2": GND, "4": "TLM", "5": "SIG1", "6": "SIG2", "7": "SIG3", "8": "SIG4"},
      mpn="SM08B-SRSS-TB")
d.add("TP", "Connector:TestPoint", "TLM", "TestPoint:TestPoint_Pad_1.0x1.0mm", {"1": "TLM"},
      note="not driven; AM32 RPM telemetry uses bidirectional DShot on SIGn")

# ---------------------------------------------------------------- 4 channels
for n in (1, 2, 3, 4):
    p = "E%d_" % n
    rail = "+10V_A" if n <= 2 else "+10V_B"
    v33 = "+3V3_%d" % n
    d.group("ESC%d MCU" % n)
    d.add("U", "MCU_ST_STM32G0:STM32G071K8UxN", "STM32G071K8U6N",
          "Package_DFN_QFN:QFN-32-1EP_5x5mm_P0.5mm_EP3.45x3.45mm",
          {"VDD": v33, "VSS": GND,
           "PA10/UCPD1_DBCC2": p + "HA", "PA9/UCPD1_DBCC1": p + "HB", "PA8": p + "HC",
           "PB15": p + "LA", "PB0": p + "LB", "PA7": p + "LC",
           "PC6": p + "SIG",
           "PA0": p + "BEMF_A", "PA2": p + "BEMF_B", "PB7": p + "BEMF_C",
           "PA1": p + "NEUTRAL", "PA3": p + "NEUTRAL",
           "PA4": GND, "PA5": p + "VSENSE",              # PA4 = current ADC: no sensor, tied low
           "PA13": p + "SWDIO", "PA14": p + "SWCLK"},
          mpn="STM32G071K8U6N", note="AM32 target JUPITER_80_G071 pinout")
    d.add("U", "Regulator_Linear:MCP1703Ax-330xxTT", "MCP1703-3.3", "Package_TO_SOT_SMD:SOT-23",
          {"3": rail, "1": GND, "2": v33}, mpn="MCP1703AT-3302E/CB")
    d.C("1uF", rail, GND, size="0603", volt="25V", lcsc="", lcsc_ok=False)
    d.C("1uF", v33, GND)
    d.C("100nF", v33, GND)
    d.R("100", "SIG%d" % n, p + "SIG")
    d.R("27.4k", "VBAT", p + "VSENSE"); d.R("1k", p + "VSENSE", GND)   # x28.4 (target 28.5)
    d.add("TP", "Connector:TestPoint", "DIO%d" % n, "TestPoint:TestPoint_Pad_1.0x1.0mm", {"1": p + "SWDIO"})
    d.add("TP", "Connector:TestPoint", "CLK%d" % n, "TestPoint:TestPoint_Pad_1.0x1.0mm", {"1": p + "SWCLK"})
    d.add("TP", "Connector:TestPoint", "3V3_%d" % n, "TestPoint:TestPoint_Pad_1.0x1.0mm", {"1": v33})

    d.group("ESC%d power stage" % n)
    for ph in "ABC":
        P_ = p + "PH_" + ph
        d.add("U", "Driver_FET:LM2105DSG", "LM2105", "Package_SON:WSON-8-1EP_2x2mm_P0.5mm_EP0.9x1.6mm",
              {"1": rail, "4": GND, "9": GND, "2": p + "H" + ph, "3": p + "L" + ph,
               "8": p + "BST_" + ph, "6": P_, "7": p + "GH_" + ph, "5": p + "GL_" + ph},
              mpn="LM2105DSGR")
        d.C("1uF", rail, GND, size="0603", volt="25V", lcsc="", lcsc_ok=False)
        d.C("220nF", p + "BST_" + ph, P_, lcsc="", lcsc_ok=False)
        d.add("Q", FET, "CSD18543Q3A", FET_FP, {"5": "VBAT", "1": P_, "2": P_, "3": P_, "4": p + "GH_" + ph},
              mpn="CSD18543Q3A", note="high side")
        d.add("Q", FET, "CSD18543Q3A", FET_FP, {"5": P_, "1": GND, "2": GND, "3": GND, "4": p + "GL_" + ph},
              mpn="CSD18543Q3A", note="low side")
        d.add("TP", "Connector:TestPoint", "M%d%s" % (n, ph), "TestPoint:TestPoint_Pad_2.5x2.5mm", {"1": P_})
        # back-EMF divider, and the virtual neutral formed from the three divided signals:
        # BEMF_k - NEUTRAL = (PH_k - mean(PH)) / 11.8  (18k / 2k / 10k), ~2.1 V at 25.2 V
        d.R("18k", P_, p + "BEMF_" + ph); d.R("2k", p + "BEMF_" + ph, GND)
        d.R("10k", p + "BEMF_" + ph, p + "NEUTRAL")
    d.C("10uF", "VBAT", GND, size="1206", volt="50V", lcsc="", lcsc_ok=False)
    d.C("100nF", "VBAT", GND, size="0603", volt="50V", lcsc="", lcsc_ok=False)

d.group("Mechanical")
for _ in range(4):
    d.add("H", "Mechanical:MountingHole", "M3", "MountingHole:MountingHole_3.2mm_M3", {})
DESIGN = d
